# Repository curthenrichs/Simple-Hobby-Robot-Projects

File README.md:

# Simple-Hobby-Robot-Projects
Most of my smaller / earlier projects in hobby robotics. These are listed in the
order of their creation (first is oldest, last is newest). This project is archived 
and will not be updated.

Please also checkout my blog here : https://www.half-built-robots.com/

### Highschool
- [BEAM Robots](./BEAM/README.md)
- [Lego-Mindstorms ~ Beta-Rex](./Lego-Mindstorms/README.md)
- [BOE-Bot](./BOE-Bot/README.md)
- [Roverbot ~ Oldest Version](./Roverbot/README.md)
- [Bubbles ~ Oldest Version](./Bubbles/README.md)

### College
- [SpinBot](./SpinBot/README.md)
- [XBee-Case](./XBee-Case/README.md)
- [Orion](./Orion/README.md)
- [PhoBo](./PhoBo/README.md)
- [Roverbot ~ Current Version](./Roverbot/README.md)

## Post-Grad
- [Roverbot ~ Fixing wear & tear](./Roverbot/README.md)
- [Bubbles ~ In Progress Version](./Bubbles/README.md)

## Note
This codebase is not well documented or maintained. I am only keeping it around
for archival purposes.

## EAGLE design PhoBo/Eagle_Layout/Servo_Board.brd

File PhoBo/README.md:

# PhoBo
This was an Eagle board layout project where I wanted to use an old phone to
directly control two motors. The goal was to use an op-amp connected to the
phones headphone jack that was wired to produce a + / - delta which in turn
caused a difference in power in the motors.

I finished the first version of the board but never got around to actually
build the robot or write the code.

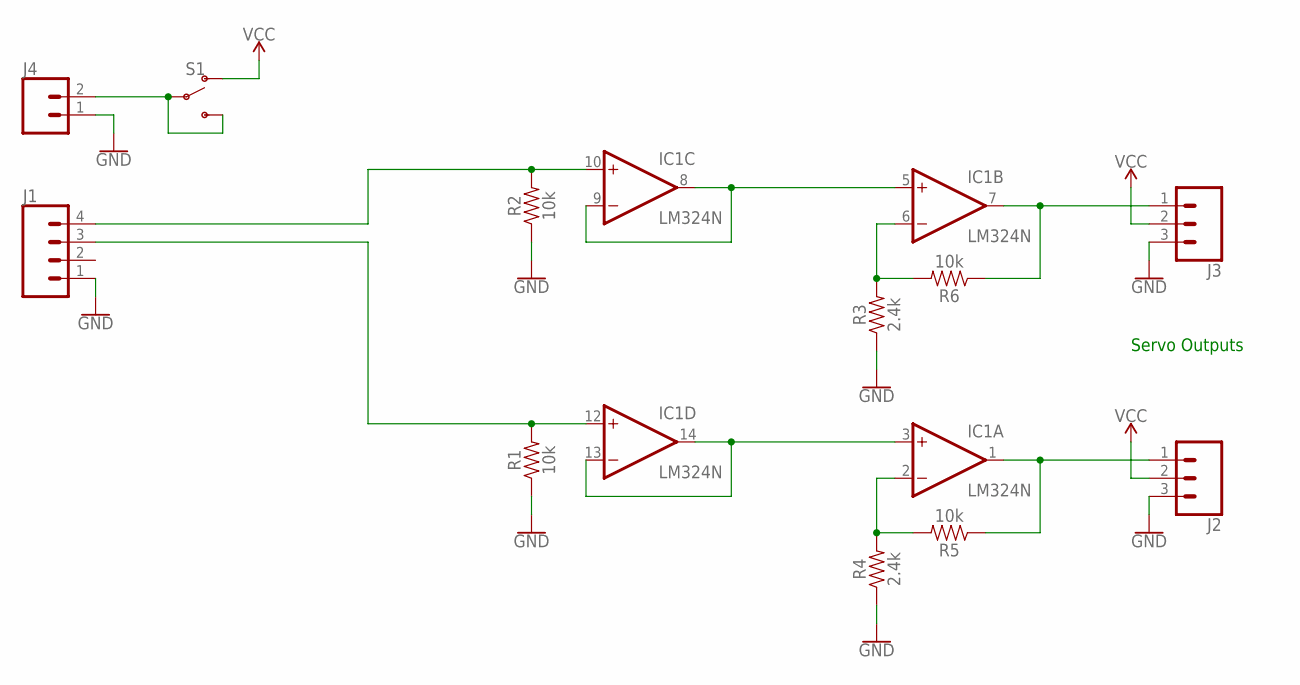
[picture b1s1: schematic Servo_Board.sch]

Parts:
IC1: LM324N; DIL14
J1: CONN_04; 1X04
J2, J3: CONN_03; 1X03
J4: CONN_02; 1X02
R1, R2, R5, R6: 10k; AXIAL-0.3
R3, R4: 2.4k; AXIAL-0.3
S1: SWITCH-SPDT-PTH-11.6X4.0MM; SWITCH_SPDT_PTH_11.6X4.0MM

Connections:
GND: IC1.11 (V-), J1.1, J2.3, J3.3, J4.1, R1.P$1 (1), R2.P$1 (1), R3.P$1 (1), R4.P$1 (1)
unnamed: IC1.5 (+IN), IC1.8 (OUT), IC1.9 (-IN)
unnamed: IC1.6 (-IN), R3.P$2 (2), R6.P$2 (2)
unnamed: J4.2, S1.2, S1.3 (S)
unnamed: IC1.10 (+IN), J1.4, R2.P$2 (2)
unnamed: IC1.2 (-IN), R4.P$2 (2), R5.P$2 (2)
unnamed: IC1.12 (+IN), J1.3, R1.P$2 (2)
unnamed: IC1.7 (OUT), J3.1, R6.P$1 (1)
unnamed: IC1.1 (OUT), J2.1, R5.P$1 (1)
unnamed: IC1.3 (+IN), IC1.13 (-IN), IC1.14 (OUT)
VCC: IC1.4 (V+), J2.2, J3.2, S1.1 (O)

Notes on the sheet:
Servo Outputs

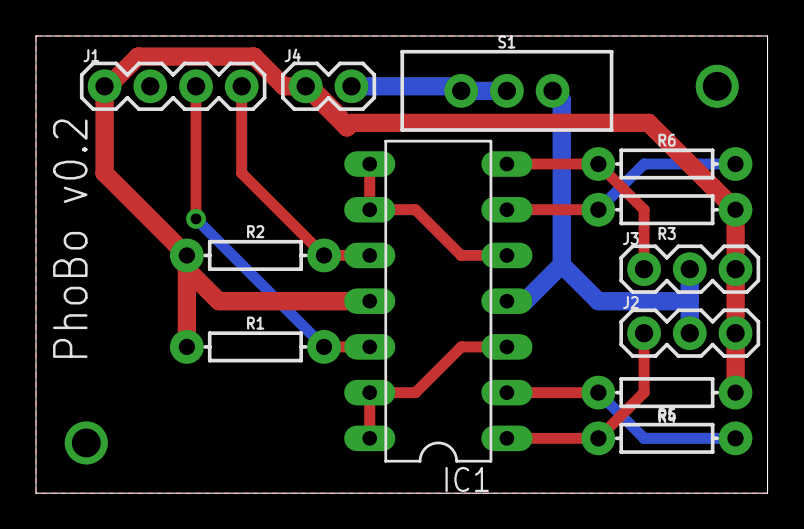
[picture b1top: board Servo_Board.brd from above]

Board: 2 copper layers, 40.6 x 25.4 mm, 12 parts (0 on the bottom side), 11 nets.

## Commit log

2021-04-03 initial commit - copying over projects
2021-04-03 stubbing repo
2021-04-04 updating documentation
2021-04-04 Create LICENSE
2021-04-10 add orion and xbee-case projects
2021-05-10 moving bubbles code into more centralized repo
2021-07-05 adding roverbot into the simple robot projects group (as it is a simple robot)
2021-07-05 updating simple robot documentation and removing / unnecessary files
2021-07-06 updating readme
2021-07-10 adding accelerometer and display to roverbot hardware - no behavior changes yet
2021-08-03 roverbot firmware now with new sensors!
2021-08-03 final changes to roverbot
2022-07-04 adding some project files that changed that I should really just ignore
2025-03-02 updating readmes + adding beam robots to repo + adding schematics to repo
2025-03-10 opening unity project for simulator - metadata changed + schematic capture
2025-03-10 adding documentation for spinbot
2025-04-06 removing old photos

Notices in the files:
parts and their libraries:
SparkFun-Resistors: Licensing: Creative Commons ShareAlike 4.0 International - https://creativecommons.org/licenses/by-sa/4.0
